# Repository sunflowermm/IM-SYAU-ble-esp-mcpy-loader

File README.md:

<h1 align="center">IM-SYAU-ble-esp-mcpy-loader</h1>

<p align="center">
  ESP32 MicroPython 采集端：BLE 信标（C3）广播 + 扫描器（S3）上报到 XRK-AGT（/device），供 IM-SYAU-Core 聚合与展示
</p>

<p align="center">
  关联项目：
  <a href="https://github.com/sunflowermm/IM-SYAU-Core">IM-SYAU-Core</a>
</p>

<p align="center">
  ESP32-C3（信标广播） · ESP32-S3（扫描上报）
</p>

---

## 与 IM-SYAU-Core 的关系

```mermaid
graph LR
  subgraph Device["ESP32 设备侧（本仓库）"]
    S3[ESP32-S3 扫描与上报]
    C3[ESP32-C3 信标广播]
  end

  subgraph Server["XRK-AGT 服务端"]
    WS["system-Core\nWebSocket /device"]
    BLE["IM-SYAU-Core\n蓝牙插件/HTTP API"]
    DB[(data/blues/ble_data.json)]
  end

  C3 -->|BLE 广播| S3
  S3 -->|type=data,data_type=ble_beacon_batch| WS
  WS -->|device.ble_beacon_batch 事件| BLE
  BLE --> DB
```

---

## 目录结构

```
IM-SYAU-ble-esp-mcpy-loader/
├── README.md
├── LICENSE
├── hardware/              # KiCad：S3 载板（与固件同仓）
│   └── im-syau/           # 主载板（插 ESP32-S3 DevKit）+ Gerber
├── esp32s3/
│   ├── boot.py            # 启动入口：检测配网/正常模式
│   ├── loader.py          # 设备加载器：WiFi + WS + 插件系统
│   ├── plugins/
│   │   ├── blue.py        # BLE 扫描并上报 ble_beacon_batch
│   │   └── base/plugin.py # 插件基类
│   └── lib/               # 依赖库（随项目上传到设备）
└── esp32c3mini/
    └── boot.py            # C3 广播脚本（模拟/固定信标）
```

导览业务（HTTP / 知识库 / www）在独立 Core：`IM-SYAU-Core`，本仓只含 **固件 + 板卡**。

---

## ESP32-S3：连接与上报

- **WebSocket 地址**：`ws://<server_host>:<server_port>/device`
- **注册**：启动后发送 `type=register`（包含 `device_id/device_type/device_name/...`）
- **数据上报**：插件通过 `loader.send_data()` 发送 `type=data` 的消息

### 上报数据协议（关键字段）

`esp32s3/plugins/blue.py` 会调用：

- `send_data('ble_beacon_batch', report)`

`report` 结构（示例字段）：

```json
{
  "timestamp": 1730000000,
  "batch": 1,
  "total_batches": 1,
  "update_interval": 2,
  "beacons": [
    {
      "mac": "AA:BB:CC:DD:EE:FF",
      "name": "ESP-C3-001",
      "online": true,
      "rssi": { "current": -58.2, "average": -58.2, "samples": 5 },
      "last_seen": 0,
      "sample_count": 123
    }
  ]
}
```

服务端（XRK-AGT）会把 `type=data,data_type=ble_beacon_batch` 转成事件：

- `device.ble_beacon_batch`（细分事件，`event_data = report`）

`IM-SYAU-Core` 的蓝牙插件监听 `device.ble_beacon_batch` 并写入 `data/blues/ble_data.json`，供前端 `/kb` 与 `/api/ble/*` 查询展示。

---

## 插件加载（默认启用所有插件）

`esp32s3/loader.py` 的插件加载逻辑：

- 当 **未配置** `enabled_plugins`（或为空）时，会扫描 `plugin_dir`（默认 `/plugins`）并 **默认启用目录下所有可用插件**（排除 `_` 前缀与 `base*`）。
- 若你希望只启用部分插件，可在设备配置里显式设置 `enabled_plugins`（例如 `["blue"]`）。

---

## 许可证

本仓库采用 [MIT License](LICENSE)。与配套项目 [`IM-SYAU-Core`](https://github.com/sunflowermm/IM-SYAU-Core) 一起作为同一套“昆虫博物馆智能导览”解决方案的组成部分。

---

## 鸣谢

本采集端固件基于 [XRK-AGT](https://github.com/sunflowermm/XRK-AGT) 框架的 `/device` 通道、
事件系统与 Core 机制完成端到端集成，感谢 XRK-AGT 项目提供可靠的底层能力。

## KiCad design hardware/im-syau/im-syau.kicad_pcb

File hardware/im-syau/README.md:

# IM-SYAU 载板（插整块 S3 开发板）

**约 54×68 mm · 4 层**。左排母插 DevKit，右列充电/开关。开发板自带 3.3 V LDO，载板不再放 AMS1117。

## 组装

1. 打板贴片本载板（4 层）  
2. 焊两排 **2.54 mm 1×22 排母**（或把开发板排针直接焊进孔）  
3. 插入 **ESP32-S3 N16R8**（DevKitC-1 兼容，排距 22.86 mm）  
4. 烧录用开发板上的 **USB**；本板 **J1** 只负责充电  

**插向（按乐鑫 DevKitC-1）**：开发板 **USB 朝 pin22（板底）**；正面朝上时 **有丝印 5V 的那一侧进 J3**（`J3.21=5V`，`J3.22=GND`）。杂牌板务必按丝印核对，勿盲插。

部分克隆板从排针灌 5 V 前需短路板上的 **5V 二极管焊盘 / N-OUT**，否则 5 V 脚灌不进去——先万用表确认。

**不要**同时用载板 `J1` 充电供电 + 开发板 USB 长时间并联（可能顶牛）；调试烧录时建议 `SW2` 断开载板 5 V。

## 开关

| 开关 | 作用 |
|---|---|
| **SW1 PWR_CUT** | 切断整机（插 USB 仍可充电池） |
| **SW2 ESP_CUT** | 切断送给开发板的 5 V |

## 购物

| 已有 | 还要买 |
|---|---|
| ESP32-S3 N16R8 核心板 | `1×22 排母 2.54mm` ×2 |
| | `TP4056` / `SS34`×2 / `USB-C 16P` / `JST-PH 2.0` / 拨码开关×2 / `0805` 阻容 LED / 保险丝 |
| | 电池：`3.7V LiPo 带保护 JST-PH` |

## 再生

在本目录（`hardware/im-syau/`）执行：

```text
python tools\build_one.py
%LOCALAPPDATA%\Programs\KiCad\10.0\bin\python.exe tools\finish_one.py
```

Gerber：`fab/gerber/`

本板与仓库根目录固件同属 **IM-SYAU-ble-esp-mcpy-loader**；导览后端 / 前端是独立项目 **IM-SYAU-Core**（`XRK-AGT/core/IM-SYAU-Core`），勿与本仓合并。

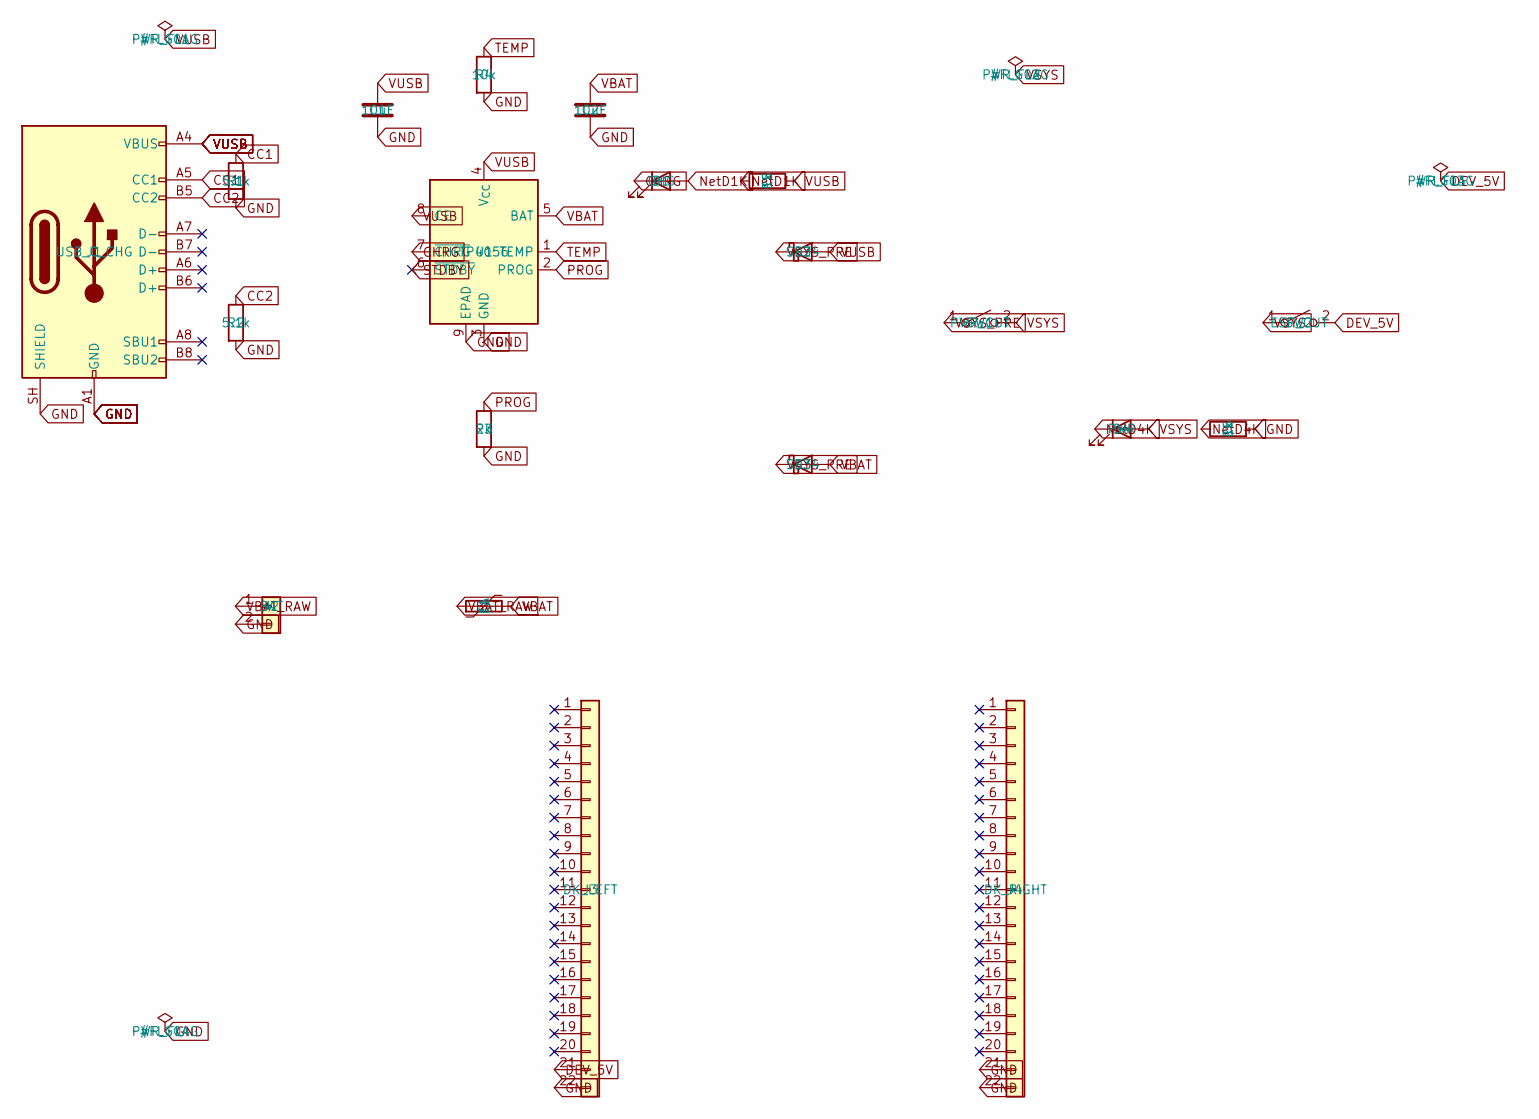
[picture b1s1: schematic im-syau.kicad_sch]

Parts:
C1, C2: 10uF; C_0805_2012Metric
D1: CHG; LED_0805_2012Metric
D2, D3: SS34; D_SMA
D4: PWR; LED_0805_2012Metric
F1: 1A; Fuse_1206_3216Metric
J1: USB_C_CHG; USB_C_Receptacle_GCT_USB4085
J2: BAT; JST_PH_B2B-PH-K_1x02_P2.00mm_Vertical
J3: DK_LEFT; PinSocket_1x22_P2.54mm_Vertical
J4: DK_RIGHT; PinSocket_1x22_P2.54mm_Vertical
R1, R2: 5.1k; R_0805_2012Metric
R3: 2k; R_0805_2012Metric
R4: 10k; R_0805_2012Metric
R5, R6: 1k; R_0805_2012Metric
SW1: PWR_CUT; SW_DIP_SPSTx01_Slide_6.7x4.1mm_W8.61mm_P2.54mm_LowProfile
SW2: ESP_CUT; SW_DIP_SPSTx01_Slide_6.7x4.1mm_W8.61mm_P2.54mm_LowProfile
U1: TP4056; SOIC-8-1EP_3.9x4.9mm_P1.27mm_EP2.41x3.3mm_ThermalVias

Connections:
CC1: J1.A5 (CC1), R1.1
CC2: J1.B5 (CC2), R2.1
CHRG: D1.1 (K), U1.7 (~CHRG)
DEV_5V: J3.21, SW2.2 (B)
GND: C1.2, C2.2, J1.A1 (GND), J1.A12 (GND), J1.B1 (GND), J1.B12 (GND), J1.SH (SHIELD), J2.2, J3.22, J4.21, J4.22, R1.2, R2.2, R3.2, R4.2, R6.2, U1.3 (GND), U1.9 (EPAD)
NetD1K: D1.2 (A), R5.1
NetD4K: D4.1 (K), R6.1
PROG: R3.1, U1.2 (PROG)
STDBY: U1.6 (~STDBY)
TEMP: R4.1, U1.1 (TEMP)
VBAT: C2.1, D3.2 (A), F1.2, U1.5 (BAT)
VBAT_RAW: F1.1, J2.1
VSYS: D4.2 (A), SW1.2 (B), SW2.1 (A)
VSYS_PRE: D2.1 (K), D3.1 (K), SW1.1 (A)
VUSB: C1.1, D2.2 (A), J1.A4 (VBUS), J1.A9 (VBUS), J1.B4 (VBUS), J1.B9 (VBUS), R5.2, U1.4 (V_{CC}), U1.8 (CE)

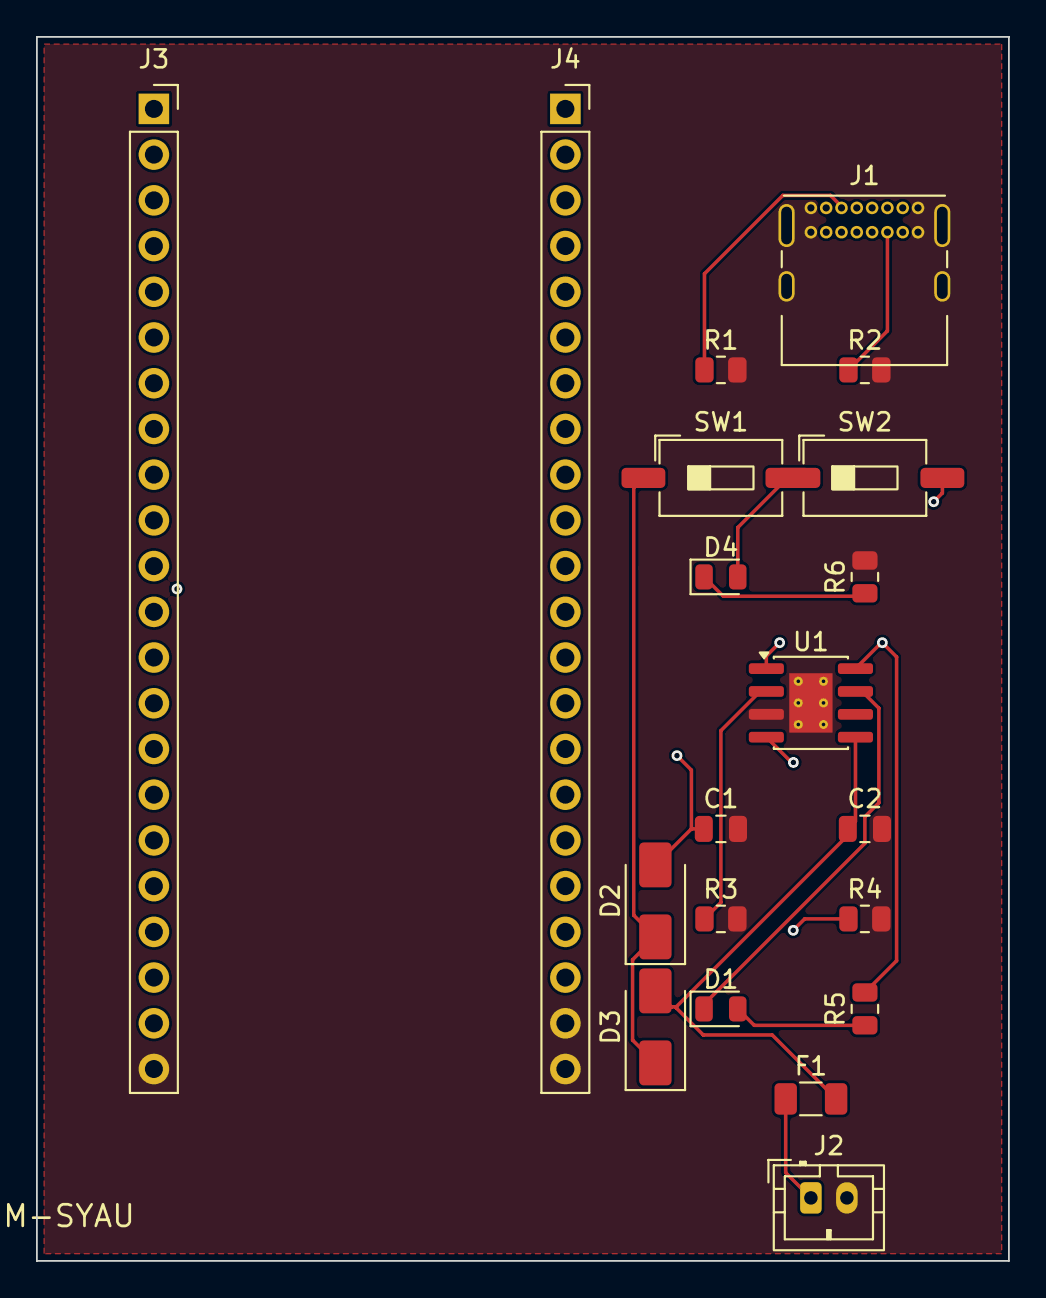
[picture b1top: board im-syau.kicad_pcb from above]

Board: 4 copper layers, 54.0 x 68.0 mm, 20 parts (0 on the bottom side), 14 nets.

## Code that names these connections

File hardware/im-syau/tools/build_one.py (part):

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            pass
    for p in ("A4", "A9", "B4", "B9"):
        try:
            connect_label("J1", p, "VUSB")
        except Exception:
            pass
    for p in ("A6", "A7", "A8", "B6", "B7", "B8", "A2", "A3", "B2", "B3"):
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    except Exception:
        pass

    connect_label("U1", "4", "VUSB")
    connect_label("U1", "3", "GND")
    connect_label("U1", "5", "VBAT")
    connect_label("U1", "2", "PROG")
    connect_label("R3", "1", "PROG")
    connect_label("R3", "2", "GND")
    connect_label("U1", "1", "TEMP")
    connect_label("R4", "1", "TEMP")
    connect_label("R4", "2", "GND")
    connect_label("U1", "8", "VUSB")
    connect_label("U1", "7", "CHRG")
    connect_label("U1", "6", "STDBY")
    try:
        connect_label("U1", "9", "GND")
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        pass
    # TP4056 CHRG is open-drain active-low: LED A→R→VUSB, K→CHRG
    # KiCad Device:LED pin1=K pin2=A
    connect_label("D1", "1", "CHRG")
    connect_label("D1", "2", "NetD1K")
    connect_label("R5", "1", "NetD1K")
    connect_label("R5", "2", "VUSB")
    connect_label("C1", "1", "VUSB")
    connect_label("C1", "2", "GND")
    connect_label("C2", "1", "VBAT")
    connect_label("C2", "2", "GND")
    connect_label("J2", "1", "VBAT_RAW")
    connect_label("J2", "2", "GND")
    connect_label("F1", "1", "VBAT_RAW")
    connect_label("F1", "2", "VBAT")
    connect_label("D2", "2", "VUSB")
    connect_label("D2", "1", "VSYS_PRE")
    connect_label("D3", "2", "VBAT")
    connect_label("D3", "1", "VSYS_PRE")
    connect_label("SW1", "1", "VSYS_PRE")
    connect_label("SW1", "2", "VSYS")
    connect_label("D4", "2", "VSYS")
    connect_label("D4", "1", "NetD4K")
    connect_label("R6", "1", "NetD4K")
    connect_label("R6", "2", "GND")
    connect_label("SW2", "1", "VSYS")
    connect_label("SW2", "2", "DEV_5V")

    # DevKitC-1: USB 端=pin21/22；正面 USB 朝下时左侧 J1 为 5V（本板 J3）
    connect_label("J3", "21", "DEV_5V")
    connect_label("J3", "22", "GND")
    connect_label("J4", "21", "GND")
    connect_label("J4", "22", "GND")
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
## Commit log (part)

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2026-02-23 Update: 2026/2/23 17:37:32 [+4099 -0 行]
2026-02-23 Update: 2026/2/23 17:40:07 [1 修改, +4 -4 行]
2026-02-23 Update: 2026/2/23 17:42:19 [1 修改, +2 -2 行]
2026-02-23 Update: 2026/2/23 17:43:57 [1 修改, +4 -0 行]
2026-02-23 Update: 2026/2/23 18:02:46 [1 修改, +7 -0 行]
